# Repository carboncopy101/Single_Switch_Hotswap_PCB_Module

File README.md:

# Single_Switch_Hotswap_PCB_Module

A simple single switch pcb for mechanical keyboard prototyping row and column matrices.
PCB features a hot swappable socket and uses a 1n4148 SMD diode.

13 Feb 2022 - did the initial BOM. Created kicad project. Finished with hotswap socket symbol and footprint. To start on schematic.

14 Feb 2022 - finished schematic and pcb. Generated gerber file. Test print and check compatibility with hotswap socket and 3/5 pin switch.

15 Feb 2022 - check if pcb within 1u keycap size(18x18mm). Need to make pcb smaller. Switch spacing. center to center is 19.05mm.

16 Feb 2022 - test print. all components line up. Move on to creating a matrix of single switch pcb. New kicad project?

18 Feb 2022 - created kicad project for single switch matrix
 
19 Feb 2022 - finished schematic and netlist. To proceed to pcb design.
## To Do
- Initial BOM (done 13 Feb 2022)
- Symbol and footprint for each component (done 14 Feb 2022)
- Schematics (done 14 Feb 2022)
- Board outline (done 14 Feb 2022)
- Board routing (done 14 Feb 2022)
- Test parts (done 16 Feb 2022)
- Create a PCB with matrix of single switch for manufacturing. (started 18 Feb 2022)

## Initial BOM
- hotswap socket (need to create library)
- 1n4148 SMD diode
- 4 pin headers (2 for column, 2 for row)
- 4 mounting holes (M3?)

## Mechanical Drawing

## Test Print

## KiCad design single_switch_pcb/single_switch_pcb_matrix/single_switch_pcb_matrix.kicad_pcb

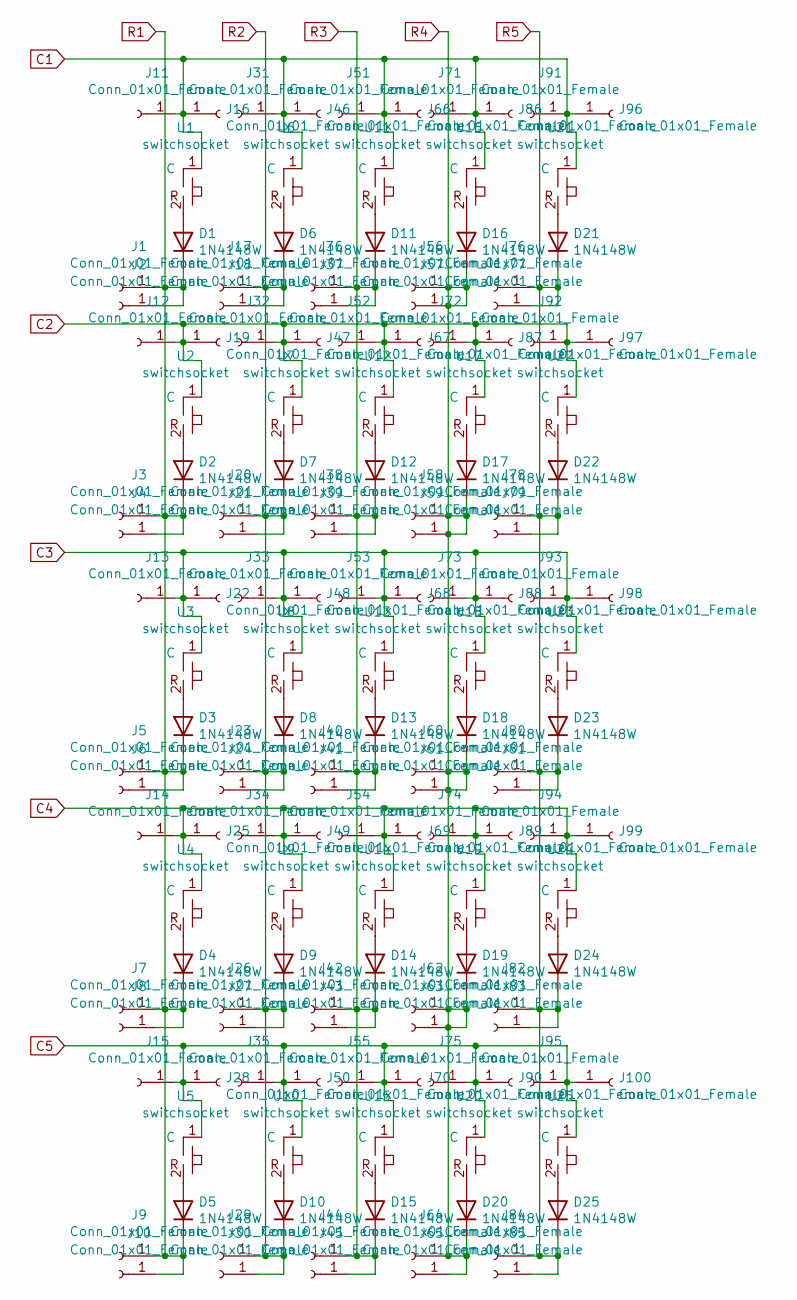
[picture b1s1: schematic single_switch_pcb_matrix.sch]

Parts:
D1, D2, D3, D4, D5, D6, D7, D8, D9, D10, D11, D12, D13, D14, D15, D16, D17, D18, D19, D20, D21, D22, D23, D24, D25: 1N4148W; D_SOD-123
J1, J2, J3, J4, J5, J6, J7, J8, J9, J10, J11, J12, J13, J14, J15, J16, J17, J18, J19, J20, J21, J22, J23, J24, J25, J26, J27, J28, J29, J30, J31, J32, J33, J34, J35, J36, J37, J38, J39, J40, J41, J42, J43, J44, J45, J46, J47, J48, J49, J50, J51, J52, J53, J54, J55, J56, J57, J58, J59, J60, J61, J62, J63, J64, J65, J66, J67, J68, J69, J70, J71, J72, J73, J74, J75, J76, J77, J78, J79, J80, J81, J82, J83, J84, J85, J86, J87, J88, J89, J90, J91, J92, J93, J94, J95, J96, J97, J98, J99, J100: Conn_01x01_Female; PinHeader_1x01_P2.54mm_Vertical
U1, U2, U3, U4, U5, U6, U7, U8, U9, U10, U11, U12, U13, U14, U15, U16, U17, U18, U19, U20, U21, U22, U23, U24, U25: switchsocket; hotswap socket

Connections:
C1: J11.1, J16.1, J31.1, J46.1, J51.1, J66.1, J71.1, J86.1, J91.1, J96.1, U1.1 (C), U6.1 (C), U11.1 (C), U16.1 (C), U21.1 (C)
C2: J12.1, J19.1, J32.1, J47.1, J52.1, J67.1, J72.1, J87.1, J92.1, J97.1, U2.1 (C), U7.1 (C), U12.1 (C), U17.1 (C), U22.1 (C)
C3: J13.1, J22.1, J33.1, J48.1, J53.1, J68.1, J73.1, J88.1, J93.1, J98.1, U3.1 (C), U8.1 (C), U13.1 (C), U18.1 (C), U23.1 (C)
C4: J14.1, J25.1, J34.1, J49.1, J54.1, J69.1, J74.1, J89.1, J94.1, J99.1, U4.1 (C), U9.1 (C), U14.1 (C), U19.1 (C), U24.1 (C)
C5: J15.1, J28.1, J35.1, J50.1, J55.1, J70.1, J75.1, J90.1, J95.1, J100.1, U5.1 (C), U10.1 (C), U15.1 (C), U20.1 (C), U25.1 (C)
unnamed: D1.2 (A), U1.2
unnamed: D2.2 (A), U2.2
unnamed: D3.2 (A), U3.2
unnamed: D4.2 (A), U4.2
unnamed: D5.2 (A), U5.2
unnamed: D6.2 (A), U6.2
unnamed: D7.2 (A), U7.2
unnamed: D8.2 (A), U8.2
unnamed: D9.2 (A), U9.2
unnamed: D10.2 (A), U10.2
unnamed: D11.2 (A), U11.2
unnamed: D12.2 (A), U12.2
unnamed: D13.2 (A), U13.2
unnamed: D14.2 (A), U14.2
unnamed: D15.2 (A), U15.2
unnamed: D16.2 (A), U16.2
unnamed: D17.2 (A), U17.2
unnamed: D18.2 (A), U18.2
unnamed: D19.2 (A), U19.2
unnamed: D20.2 (A), U20.2
unnamed: D21.2 (A), U21.2
unnamed: D22.2 (A), U22.2
unnamed: D23.2 (A), U23.2
unnamed: D24.2 (A), U24.2
unnamed: D25.2 (A), U25.2
R1: D1.1 (K), D2.1 (K), D3.1 (K), D4.1 (K), D5.1 (K), J1.1, J2.1, J3.1, J4.1, J5.1, J6.1, J7.1, J8.1, J9.1, J10.1
R2: D6.1 (K), D7.1 (K), D8.1 (K), D9.1 (K), D10.1 (K), J17.1, J18.1, J20.1, J21.1, J23.1, J24.1, J26.1, J27.1, J29.1, J30.1
R3: D11.1 (K), D12.1 (K), D13.1 (K), D14.1 (K), D15.1 (K), J36.1, J37.1, J38.1, J39.1, J40.1, J41.1, J42.1, J43.1, J44.1, J45.1
R4: D16.1 (K), D17.1 (K), D18.1 (K), D19.1 (K), D20.1 (K), J56.1, J57.1, J58.1, J59.1, J60.1, J61.1, J62.1, J63.1, J64.1, J65.1
R5: D21.1 (K), D22.1 (K), D23.1 (K), D24.1 (K), D25.1 (K), J76.1, J77.1, J78.1, J79.1, J80.1, J81.1, J82.1, J83.1, J84.1, J85.1

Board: 2 copper layers, 150 parts (0 on the bottom side), 35 nets, no tracks yet.

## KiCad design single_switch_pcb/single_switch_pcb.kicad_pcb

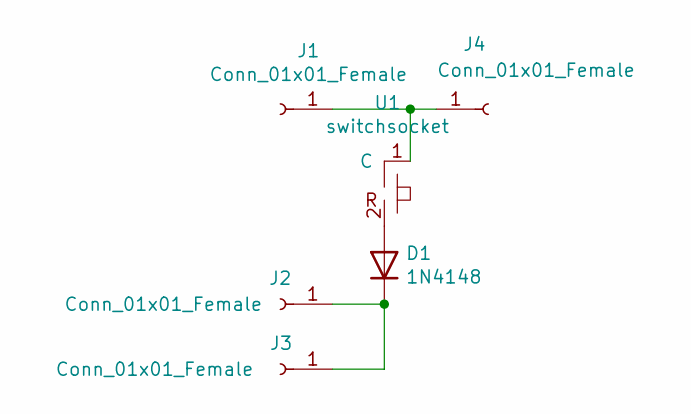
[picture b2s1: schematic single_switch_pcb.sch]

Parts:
D1: 1N4148; D_SOD-123
J1, J2, J3, J4: Conn_01x01_Female; PinHeader_1x01_P2.54mm_Vertical
U1: switchsocket; hotswap socket

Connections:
unnamed: D1.1 (K), J2.1, J3.1
unnamed: D1.2 (A), U1.2
unnamed: J1.1, J4.1, U1.1 (C)

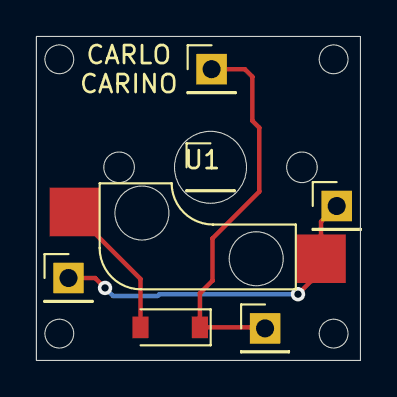
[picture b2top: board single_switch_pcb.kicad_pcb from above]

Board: 2 copper layers, 18.0 x 18.0 mm, 6 parts (0 on the bottom side), 3 nets.

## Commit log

2022-02-12 added image folder containing mechanical drawings
2022-02-12 added readme contents with plans and mechanical drawings
2022-02-13 initial BOM done. Kicad project done. to proceed to creating libraries
2022-02-13 created hotswap socket symbol
2022-02-13 done with hotswap socket footprint
2022-02-13 edited symbol footprint pinout numbers
2022-02-13 updated readme on progress
2022-02-14 basic schematic done. start with board design
2022-02-14 created netlist. assigned footprints as well. how about mounting
2022-02-14 created pcb. find key switch footprint outline. add holes. add mounting
2022-02-14 added 5 pin switch mechanical drawing. make pcb support 5 pins
2022-02-14 finished routing. need to put M3 mounting holes on each corner then do checks if design is indeed compatible
2022-02-14 finished pcb with M3 mounting. cleaned silkscreen. Need to print and test compatibility
2022-02-14 edited readme to show sample gerber file. progress report added to readme. Almost finished. Need to test compatibility
2022-02-15 realized pcb must be within 1u keycap size. check pls.
2022-02-15 added spacing between switches. 19.05mm or 0.75in
2022-02-15 edited pcb outline. needs smaller holes. created M2 and M1.6 holes
2022-02-15 m2 still big change to m1.6
2022-02-15 new design, gerber files updated, readme picture gerber sample updated
2022-02-16 added tests image. looks good. move to matrix of single switch
2022-02-18 created kicad project for switch matrix. lets make it 100x100 so it will be cheap to manufacture. 5USD 10 pcs
2022-02-18 update on readme
2022-02-18 schematic. added hotswap and diodes. pin header and routing next
2022-02-19 pcb matrix. done with column matrix. To do row matrix
2022-02-19 done with row matrix. checked lines as well. move on to netlist
2022-02-19 done with netlist. assigned footprints as well. move on to pcb desigh
2022-02-19 updated readme on the progress
2022-02-20 started pcb. work on outline or cutouts?
